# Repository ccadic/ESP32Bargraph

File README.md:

# ESP32Bargraph
Kicad Gerber files for an ESP32 Bargraph PCB with 1206 LEDS

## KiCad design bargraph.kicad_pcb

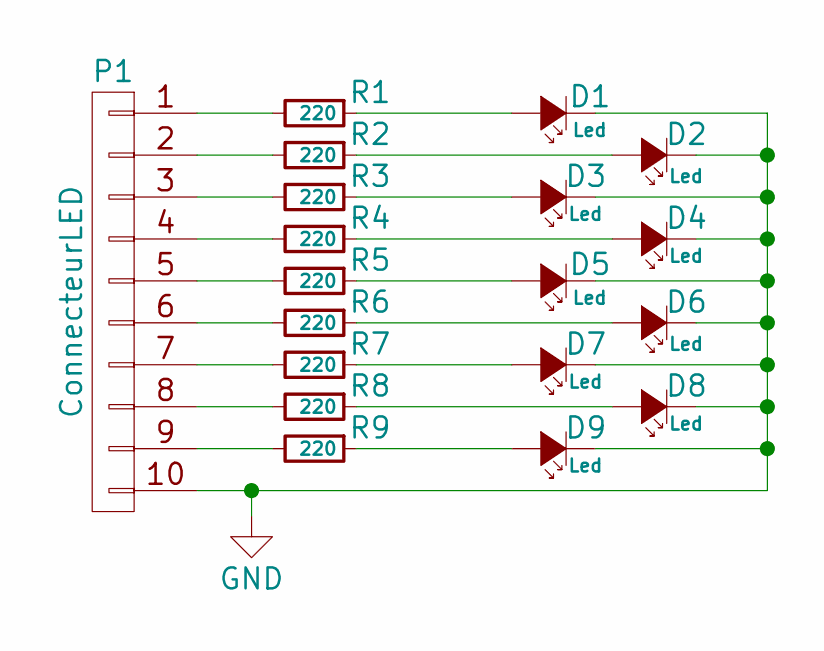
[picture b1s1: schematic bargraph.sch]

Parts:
D1, D2, D3, D4, D5, D6, D7, D8, D9: Led; LED_1206_HandSoldering
P1: ConnecteurLED; Socket_Strip_Straight_1x10_Pitch2.54mm
R1, R2, R3, R4, R5, R6, R7, R8, R9: 220; R_1206_HandSoldering

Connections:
GND: D1.1 (K), D2.1 (K), D3.1 (K), D4.1 (K), D5.1 (K), D6.1 (K), D7.1 (K), D8.1 (K), D9.1 (K), P1.10
unnamed: D1.2 (A), R1.1
unnamed: D2.2 (A), R2.1
unnamed: D3.2 (A), R3.1
unnamed: D4.2 (A), R4.1
unnamed: D5.2 (A), R5.1
unnamed: D6.2 (A), R6.1
unnamed: D7.2 (A), R7.1
unnamed: D8.2 (A), R8.1
unnamed: D9.2 (A), R9.1
unnamed: P1.1, R1.2
unnamed: P1.2, R2.2
unnamed: P1.3, R3.2
unnamed: P1.4, R4.2
unnamed: P1.5, R5.2
unnamed: P1.6, R6.2
unnamed: P1.7, R7.2
unnamed: P1.8, R8.2
unnamed: P1.9, R9.2

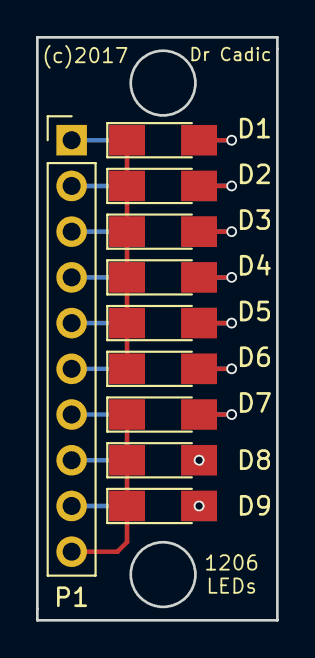
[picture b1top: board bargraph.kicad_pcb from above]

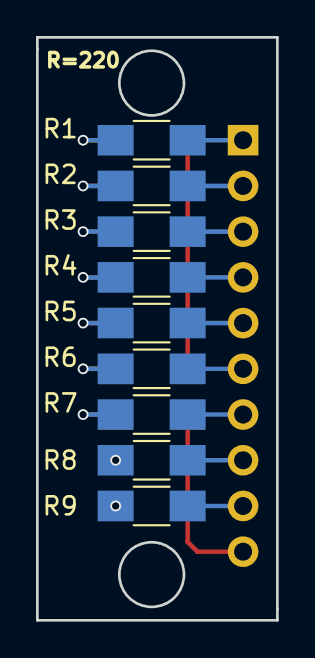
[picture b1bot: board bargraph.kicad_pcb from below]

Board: 2 copper layers, 13.3 x 32.4 mm, 19 parts (9 on the bottom side), 19 nets.

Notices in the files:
bargraph.kicad_pcb:
(c)2017
